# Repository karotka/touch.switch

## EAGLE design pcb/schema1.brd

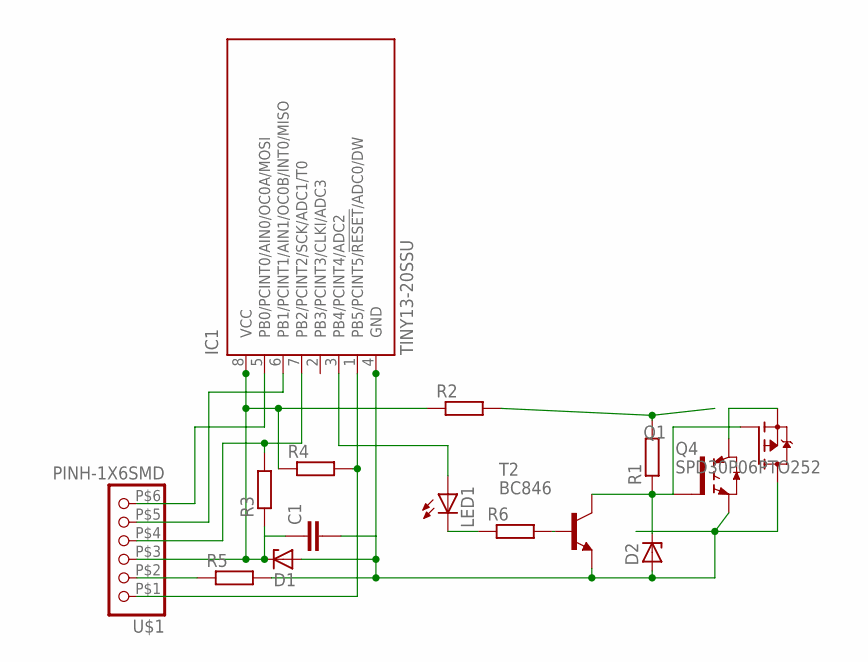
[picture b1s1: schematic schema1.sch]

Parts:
C1: C-EUC0603; C0603
D1, D2: ZENER-DIODESOD80C; SOD80C
IC1: TINY13-20SSU; 8S1
LED1: LEDSML1206; SML1206
Q1: IRG4BC15UD-S; D2PACK
Q4: SPD30P06PTO252; TO252
R1, R2, R3, R4, R5, R6: R-EU_R1206; R1206
T2: BC846; SOT23
U$1: PINH-1X6SMD; 1X06/90SMD

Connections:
unnamed: D2.C, Q1.1 (G), Q4.1 (G), R1.1, T2.3 (C)
unnamed: R6.2, T2.1 (B)
unnamed: IC1.3 (PB4/PCINT4/ADC2), LED1.A
unnamed: C1.2, D1.A, D2.A, IC1.4 (GND), Q1.3 (E), Q4.3 (D), R5.2, T2.2 (E)
unnamed: C1.1, D1.C, IC1.8 (VCC), R2.1, R3.1, R4.1, U$1.P$3 (3)
unnamed: IC1.7 (PB2/PCINT2/SCK/ADC1/T0), R3.2, U$1.P$4 (4)
unnamed: IC1.1 (PB5/PCINT5/!RESET!/ADC0/DW), R4.2, U$1.P$1 (1)
unnamed: R1.2, R2.2
unnamed: LED1.C, R6.1
unnamed: R5.1, U$1.P$2 (2)
unnamed: IC1.6 (PB1/PCINT1/AIN1/OC0B/INT0/MISO), U$1.P$5 (5)
unnamed: IC1.5 (PB0/PCINT0/AIN0/OC0A/MOSI), U$1.P$6 (6)
unnamed: Q1.2 (C), Q4.2 (S)

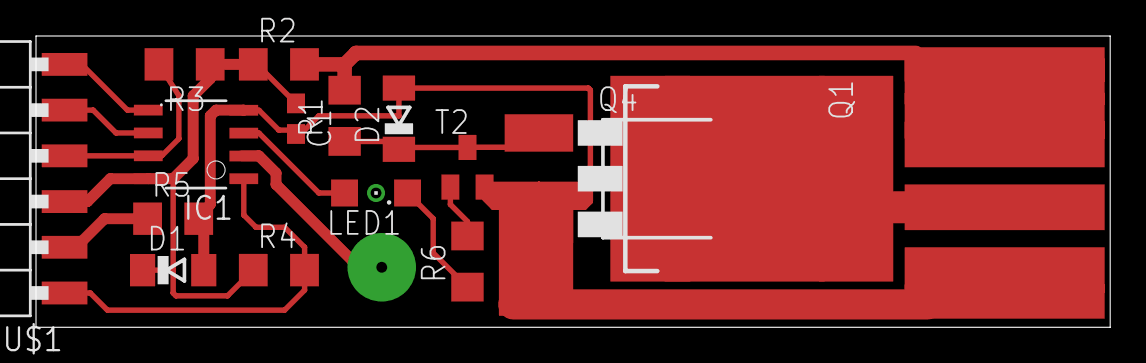
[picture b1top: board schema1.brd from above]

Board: 2 copper layers, 59.7 x 16.2 mm, 15 parts (0 on the bottom side), 13 nets.

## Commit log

2013-12-09 second commit
